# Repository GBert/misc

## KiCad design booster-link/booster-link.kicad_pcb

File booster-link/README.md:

Einfacher Gleisboxbooster
=========================

Siehe auch:
[Stummi Forum Thread](https://stummiforum.de/viewtopic.php?f=7&t=160368&start=50#p1859777)

Optionen:
- ohne öffnen der Gleisbox 
- automatishce Gleisspannungsabschaltung (Stopp) nach 250ms
- direkte Anbindung an die Gleisbox (nur zwei Widerstände + Transistor)

BOM
---
[Reichelt Liste](https://www.reichelt.de/my/1491385)

|Reference	| Value		| Footprint	|
|---------------|---------------|---------------|
|C1,C3,C11	|100nF		|RM2.5		|
|C2		|10uF		|RM2.5		|
|C12		|2,2uF		|MKS 2, RM5	|
|D1		|1N4148		|DO33		|
|D2,D3		|LED 2mA	|5mm		|
|Q1		|BC337		|TO-92		|
|R1,R3,R5,R7	|1k5 Ohm	|0207		|
|R2,R4		|390 Ohm	|0207		|
|R11,R12	|100 kOhm	|0207		|
|U1		|MC7805		|TO-220		|
|U2		|6N137		|DIP-8		|
|U3		|NE555		|DIP-8		|
|P1		|Anreihklemme	|RM5.04		|
|P2		|Pinsocket 2x4	|RM2.54		|
|P3		|Pinheader 2x3	|RM2.54		|
|P4		|Pinheader 1x3	|RM2.54		|
|		|Jumper		|RM2.54		|
|		|Spcket		|DIP-8		|

BOM (über interne Signale der Gleisbox)
---------------------------------------
|Reference	| Value		| Footprint	|
|---------------|---------------|---------------|
|Q21		|BC337		|TO-92		|
|R21		|1k5 Ohm	|0207		|
|R22		|390 Ohm	|0207		|

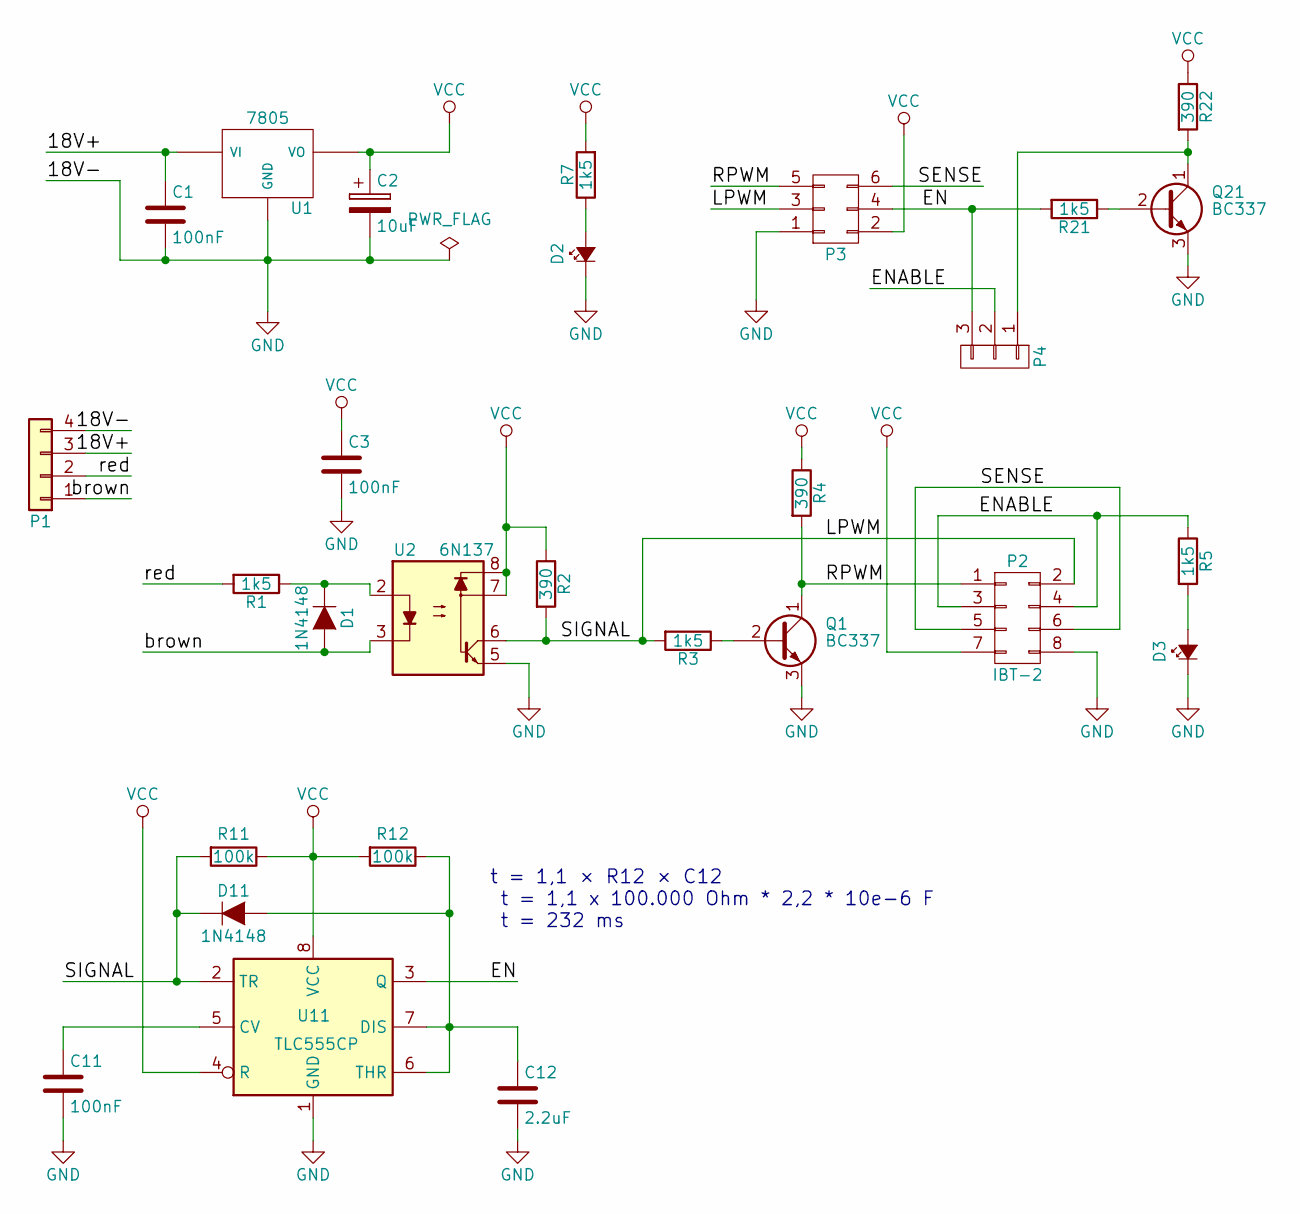
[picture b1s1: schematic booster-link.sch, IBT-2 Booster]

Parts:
C1, C3, C11: 100nF; cnp_3mm_disc
C2: 10uF; CP_4x5mm
C12: 2.2uF; C_Rect_L7_W2_P5
D1, D11: 1N4148; diode_do35
D2, D3: Led_Small; LED-5MM
P1: Conn_01x04; akl0711,5-4
P2: IBT-2; Socket_Strip_Straight_2x04
P3: EXTCON; Pin_Header_Straight_2x03
P4: CONN_01X03; Pin_Header_Straight_1x03
Q1, Q21: BC337; TO-92_Inline_Narrow_Oval
R1, R3, R5, R7, R21: 1k5; RC03
R2, R4, R22: 390; RC03
R11, R12: 100k; RC03
U1: 7805; TO-220-78xx
U2: 6N137; dil_8-300_socket
U11: TLC555CP; dil_8-300_socket

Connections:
/18V+: C1.1, P1.3, U1.VI
/EN: P3.4, P4.3, R21.2, U11.3 (Q)
/ENABLE: P2.3, P2.4, P4.2, R5.1
/LPWM: D11.2 (K), P2.2, P3.3, R2.2, R3.2, R11.2, U2.6, U11.2 (TR)
/RPWM: P2.1, P3.5, Q1.1 (C), R4.2
/SENSE: P2.5, P2.6, P3.6
/brown: D1.1 (A), P1.1, U2.3
/red: P1.2, R1.2
GND: C1.2, C2.2, C3.2, C11.2, C12.2, D2.1 (K), D3.1 (K), P1.4, P2.8, P3.1, Q1.3 (E), Q21.3 (E), U1.GND, U2.5, U11.1 (GND)
unnamed: C11.1, U11.5 (CV)
unnamed: C12.1, D11.1 (A), R12.1, U11.6 (THR), U11.7 (DIS)
unnamed: D1.2 (K), R1.1, U2.2
unnamed: D2.2 (A), R7.1
unnamed: D3.2 (A), R5.2
unnamed: P4.1, Q21.1 (C), R22.2
unnamed: Q1.2 (B), R3.1
unnamed: Q21.2 (B), R21.1
VCC: C2.1, C3.1, P2.7, P3.2, R2.1, R4.1, R7.2, R11.1, R12.2, R22.1, U1.VO, U2.7, U2.8, U11.4 (R), U11.8 (VCC)

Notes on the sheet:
t = 1,1 × R12 × C12 t = 1,1 x 100.000 Ohm * 2,2 * 10e-6 F t = 232 ms

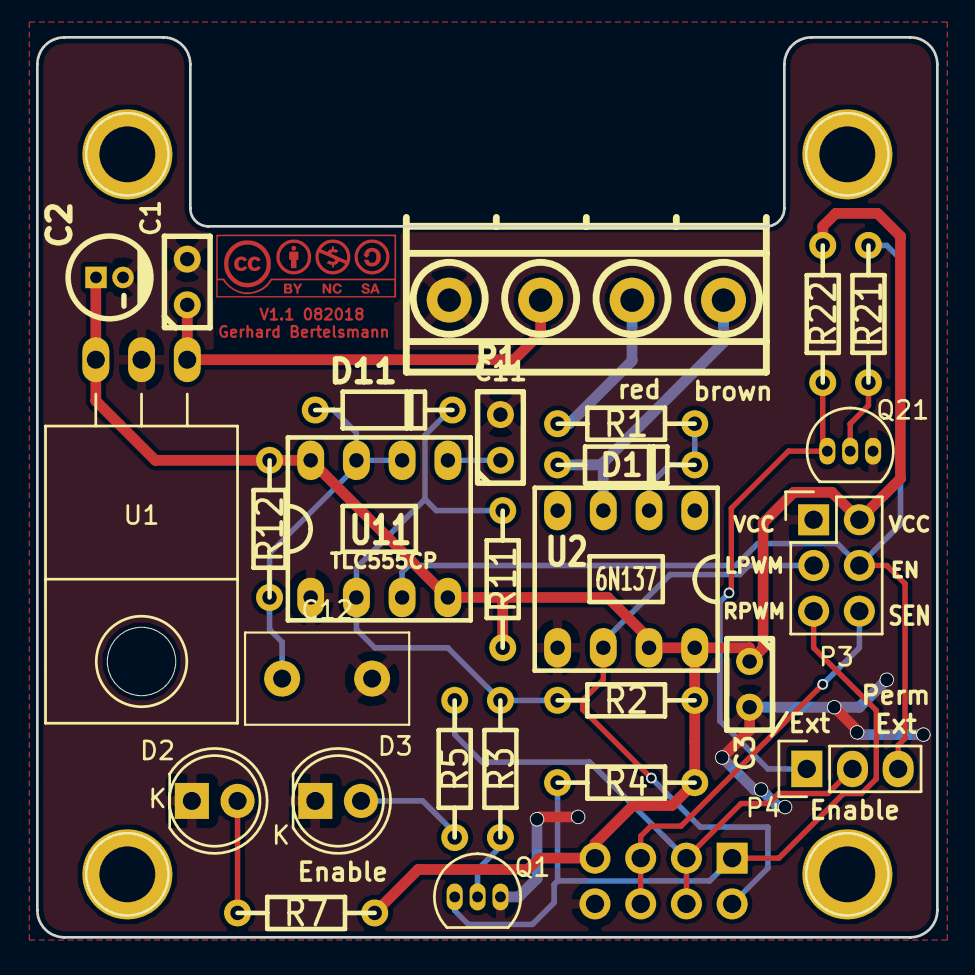
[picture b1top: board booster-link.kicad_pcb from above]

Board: 2 copper layers, 50.0 x 50.0 mm, 28 parts (1 on the bottom side), 18 nets.

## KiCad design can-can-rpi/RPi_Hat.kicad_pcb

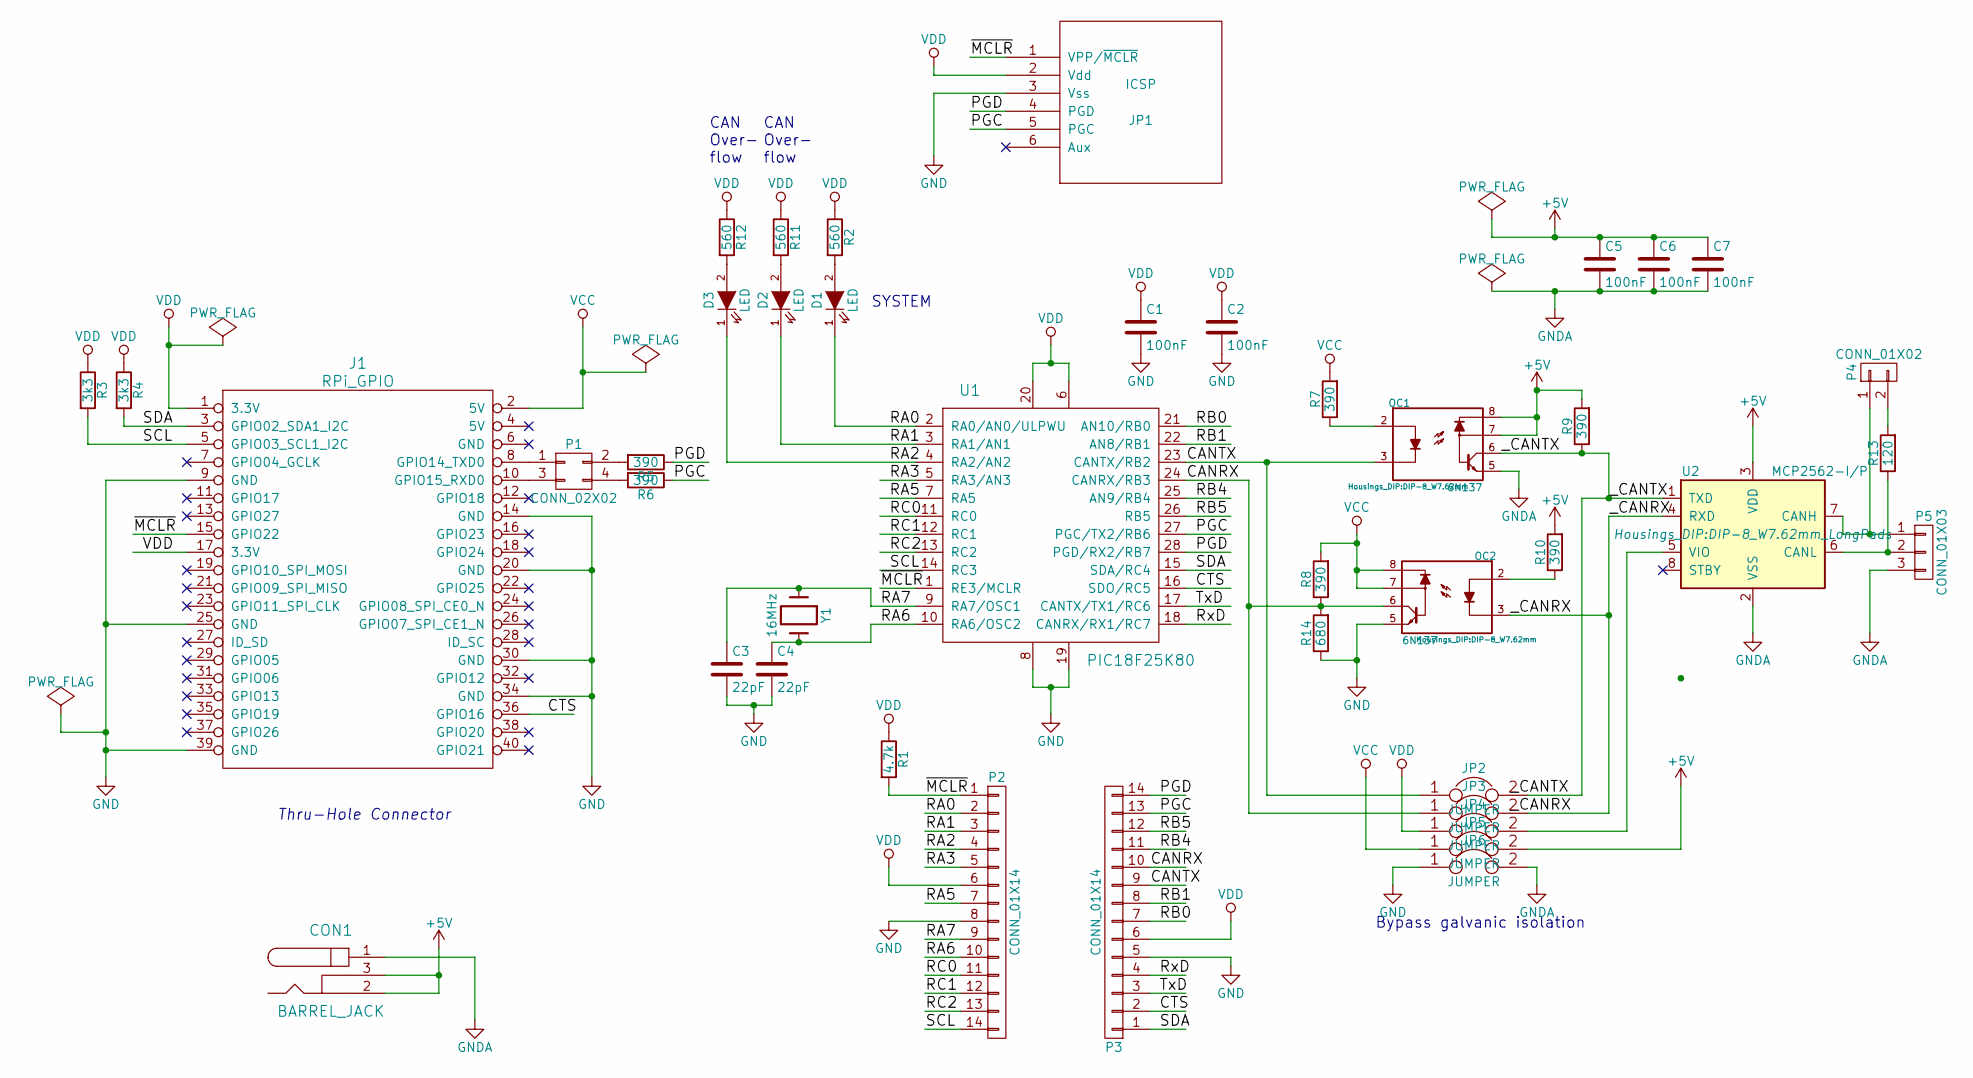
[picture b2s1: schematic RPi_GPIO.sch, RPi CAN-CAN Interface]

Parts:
C1, C2, C5, C6, C7: 100nF; C_Disc_D3_P2.5
C3, C4: 22pF; C_Disc_D3_P2.5
CON1: BARREL_JACK
D1, D2, D3: LED; LED-3MM
J1: RPi_GPIO; Socket_Strip_Straight_2x20
JP1: ICSP
JP2, JP3, JP4, JP5, JP6: JUMPER; SolderWirePad_2x_0-2.54mmDrill
OC1, OC2: 6N137; DIP-8_W7.62mm
P1: CONN_02X02; Pin_Header_Straight_2x02
P2, P3: CONN_01X14; Socket_Strip_Straight_1x14
P4: CONN_01X02; Pin_Header_Straight_1x02
P5: CONN_01X03; Pin_Header_Straight_1x03
R1: 4.7k; Resistor_Horizontal_RM10mm
R2, R11, R12: 560; Resistor_Horizontal_RM10mm
R3, R4: 3k3; Resistor_Horizontal_RM10mm
R5, R6, R7, R8, R9, R10: 390; Resistor_Horizontal_RM10mm
R13: 120; Resistor_Horizontal_RM10mm
R14: 680; Resistor_Horizontal_RM10mm
U1: PIC18F25K80; DIP-28_W7.62mm
U2: MCP2562-I/P; DIP-8_W7.62mm_LongPads
Y1: 16MHz; Crystal_HC49-U_Vertical

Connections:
+5V: C5.1, C6.1, C7.1, CON1.2, CON1.3, JP5.2, OC1.7, OC1.8, R9.2, R10.2, U2.3 (VDD)
/RPi_GPIO/CANRX: JP3.1, OC2.6, P3.10, R8.1, R14.2, U1.24 (CANRX/RB3)
/RPi_GPIO/CANTX: JP2.1, OC1.3, P3.9, U1.23 (CANTX/RB2)
/RPi_GPIO/CTS: J1.36 (GPIO16), P3.2, U1.16 (SDO/RC5)
/RPi_GPIO/PGC: JP1.5 (PGC), P3.13, R6.1, U1.27 (PGC/TX2/RB6)
/RPi_GPIO/PGD: JP1.4 (PGD), P3.14, R5.1, U1.28 (PGD/RX2/RB7)
/RPi_GPIO/RA0: D1.1 (K), P2.2, U1.2 (RA0/AN0/ULPWU)
/RPi_GPIO/RA1: D2.1 (K), P2.3, U1.3 (RA1/AN1)
/RPi_GPIO/RA2: D3.1 (K), P2.4, U1.4 (RA2/AN2)
/RPi_GPIO/RA3: P2.5, U1.5 (RA3/AN3)
/RPi_GPIO/RA5: P2.7, U1.7 (RA5)
/RPi_GPIO/RA6: C4.1, P2.10, U1.10 (RA6/OSC2), Y1.2
/RPi_GPIO/RA7: C3.1, P2.9, U1.9 (RA7/OSC1), Y1.1
/RPi_GPIO/RB0: P3.7, U1.21 (AN10/RB0)
/RPi_GPIO/RB1: P3.8, U1.22 (AN8/RB1)
/RPi_GPIO/RB4: P3.11, U1.25 (AN9/RB4)
/RPi_GPIO/RB5: P3.12, U1.26 (RB5)
/RPi_GPIO/RC0: P2.11, U1.11 (RC0)
/RPi_GPIO/RC1: P2.12, U1.12 (RC1)
/RPi_GPIO/RC2: P2.13, U1.13 (RC2)
/RPi_GPIO/RxD: P3.4, U1.18 (CANRX/RX1/RC7)
/RPi_GPIO/SCL: J1.5 (GPIO03_SCL1_I2C), P2.14, R3.2, U1.14 (RC3)
/RPi_GPIO/SDA: J1.3 (GPIO02_SDA1_I2C), P3.1, R4.2, U1.15 (SDA/RC4)
/RPi_GPIO/TxD: P3.3, U1.17 (CANTX/TX1/RC6)
/RPi_GPIO/_CANRX: JP3.2, OC2.3, U2.4 (RXD)
/RPi_GPIO/_CANTX: JP2.2, OC1.6, R9.1, U2.1 (TXD)
/RPi_GPIO/~MCLR: J1.15 (GPIO22), JP1.1 (VPP/~MCLR), P2.1, R1.2, U1.1 (RE3/MCLR)
GND: C1.2, C2.2, C3.2, C4.2, J1.9 (GND), J1.14 (GND), J1.20 (GND), J1.25 (GND), J1.30 (GND), J1.34 (GND), J1.39 (GND), JP1.3 (Vss), JP6.1, OC2.5, P2.8, P3.5, R14.1, U1.8, U1.19
GNDA: C5.2, C6.2, C7.2, CON1.1, JP6.2, OC1.5, P5.3, U2.2 (VSS)
unnamed: D1.2 (A), R2.2
unnamed: D2.2 (A), R11.2
unnamed: D3.2 (A), R12.2
unnamed: J1.8 (GPIO14_TXD0), P1.1
unnamed: J1.10 (GPIO15_RXD0), P1.3
unnamed: JP4.2, U2.5 (VIO)
unnamed: OC1.2, R7.1
unnamed: OC2.2, R10.1
unnamed: P1.2, R5.2
unnamed: P1.4, R6.2
unnamed: P4.1, P5.1, U2.7 (CANH)
unnamed: P4.2, R13.2
unnamed: P5.2, R13.1, U2.6 (CANL)
VCC: J1.2 (5V), JP5.1, OC2.7, OC2.8, R7.2, R8.2
VDD: C1.1, C2.1, J1.1 (3.3V), J1.17 (3.3V), JP1.2 (Vdd), JP4.1, P2.6, P3.6, R1.1, R2.1, R3.1, R4.1, R11.1, R12.1, U1.6, U1.20

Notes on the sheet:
Thru-Hole Connector
Bypass galvanic isolation
SYSTEM
CAN Over- flow

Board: 2 copper layers, 42 parts (1 on the bottom side), 43 nets, no tracks yet.

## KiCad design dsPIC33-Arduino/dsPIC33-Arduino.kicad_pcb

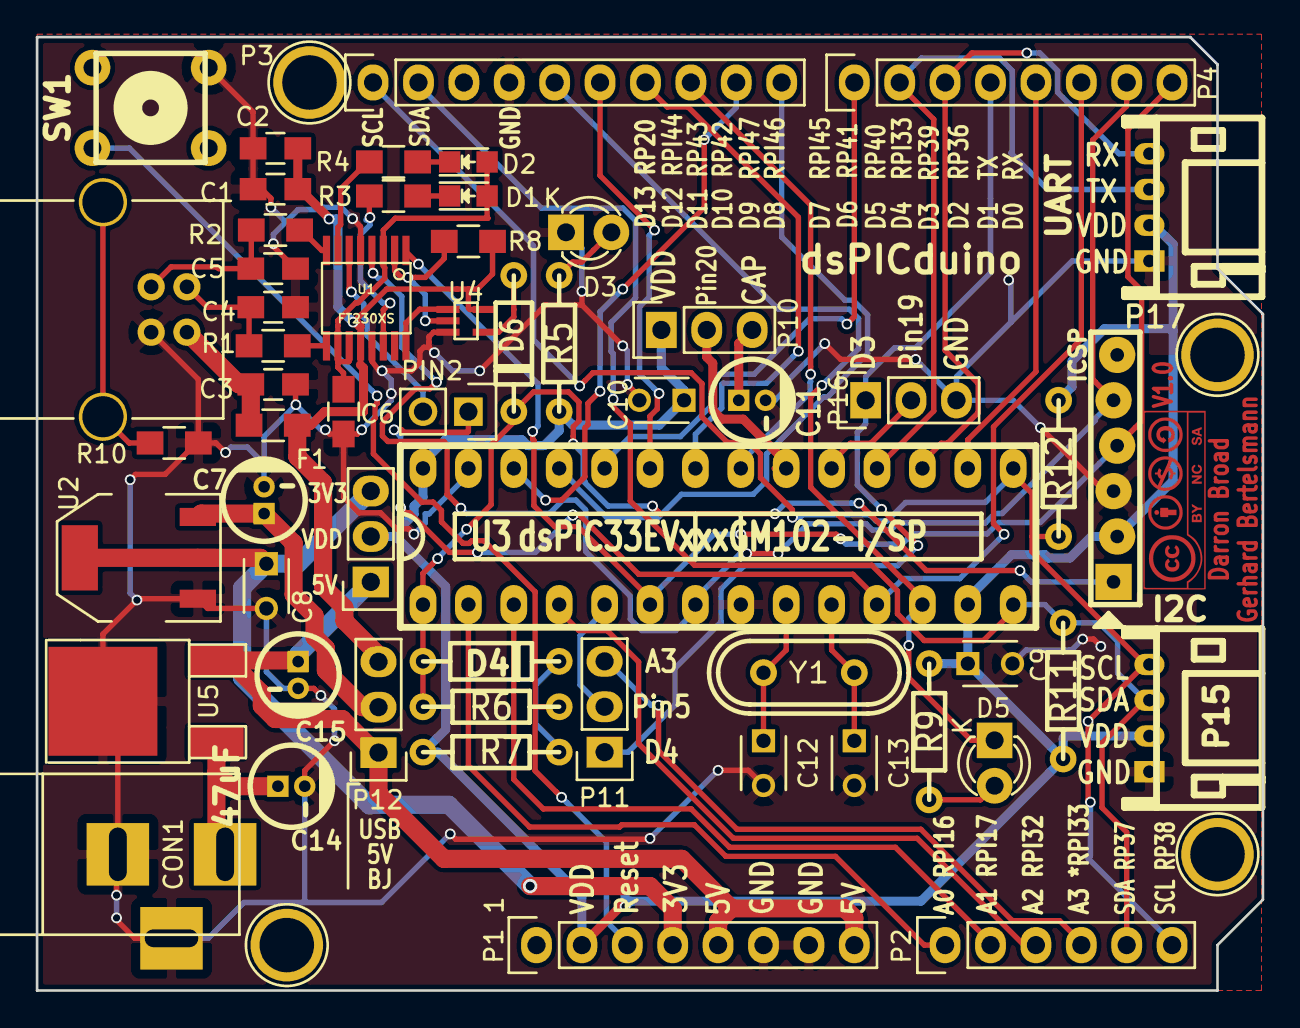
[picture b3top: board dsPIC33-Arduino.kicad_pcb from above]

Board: 2 copper layers, 68.6 x 53.3 mm, 60 parts (0 on the bottom side), 53 nets.

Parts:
C1, C6: 100nF; C_0805_HandSoldering
C2: 4,7uF; C_0805_HandSoldering
C3: 10nF; C_0805_HandSoldering
C4, C5: 47pF; C_0805_HandSoldering
C7, C14, C15: 47uF; CP_4x5mm
C8, C9, C10: 100nF; C_Disc_D3_P2.5
C11: 10uF ESR; CP_4x5mm
C12, C13: 22pF; C_Disc_D3_P2.5
CON1: BARREL_JACK
D1: RX LED; LED_0805
D2: TX LED; LED_0805
D3: Power LED; LED-3MM
D4, D6: BAT43; diode_do35
D5: LED; LED-3MM
F1: Ferrit; R_0805_HandSoldering
JP1: ICSP
P1: Power; Socket_Strip_Arduino_1x08
P2: Analog; Socket_Strip_Arduino_1x06
P3: Digital; Socket_Strip_Arduino_1x10
P4: Digital; Socket_Strip_Arduino_1x08
P5, P6, P7, P8: CONN_1; Arduino_1pin
P9: USB_B
P10: PIN20; Pin_Header_Straight_1x03
P11: PIN5; Pin_Header_Straight_1x03
P12: PWR_IN; Pin_Header_Straight_1x03
P13: PIN2; Pin_Header_Straight_1x02
P14: Power Select; Pin_Header_Straight_1x03
P15: I2C; s4b-ph-kl
P16: PIN19; Pin_Header_Straight_1x03
P17: UART; s4b-ph-kl
R1, R2: 27; R_0805_HandSoldering
R3, R4: 270; R_0805_HandSoldering
R5, R9: 1k5; RC03
R6: 470; RC03
R7: 4k7; RC03
R8: 4k7; R_0805_HandSoldering
R10: 0; R_0805_HandSoldering
R11, R12: 3k3; RC03
SW1: SW_PUSH; PCB_PUSH
U1: FT230XS; ssop-16
U2: LM1117 3V3; SOT-223
U3: dsPIC33EVxxxGM102-I/SP; dil_28-300_socket
U4: 74LVC1G32; SOT-353
U5: 7805; TO-252-2Lead
Y1: Crystal; crystal_hc-49s

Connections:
+3V3: C8.1, P1.4, P14.3, U2.2
+5V: C15.1, P1.5, P1.8, P12.1, P14.1, U5.VO
/2: P4.6, P13.1, U3.11
/3(**): P4.5, U3.16
/4: P4.4, P11.1, P16.1
/5(**): P4.3, P17.4, U3.17
/6(**): P4.2, P17.3, U3.18
/7: P4.1, U3.24
/8: P3.10, U3.25
/9(**): P3.9, U3.26
/10(**/SS): P3.8, U3.21
/11(**/MOSI): P3.7, U3.22
/12(MISO): P3.6, U3.23
/13(SCK): D5.1, P3.5, U3.12
/A0: P2.1, U3.2
/A1: P2.2, U3.3
/A2: P2.3, U3.4
/A3: P2.4, P11.3
/CTS: P13.2, U1.6
/PrgEn: U1.16, U4.1
/RTS: R8.1, U1.2, U4.2
/RX: JP1.4, P4.8, U1.1, U3.6
/SCL: P2.6, P3.1, P15.4, R12.2, U3.15
/SDA: P2.5, P3.2, P15.3, R11.2, U3.14
/TX: JP1.5, P4.7, U1.4, U3.7
/VI: C14.1, CON1.1, U5.VI
/~MCLR~: D4.1, D6.2, JP1.1, R6.1, U3.1
/~RESET~: P1.3, R6.2, SW1.2
GND: C1.2, C2.2, C3.2, C4.2, C5.2, C6.2, C7.2, C8.2, C9.2, C10.2, C11.2, C12.2, C13.2, C14.2, C15.2, CON1.2, CON1.3, D3.1, JP1.3, P1.6, P1.7, P3.4, P9.4, P15.1, P16.3, P17.1, R10.1, SW1.1, U1.5, U1.13, U2.1, U3.8, U3.27, U4.3, U5.GND
unnamed: C3.1, F1.2, P9.1
unnamed: C4.1, P9.2, R1.2
unnamed: C5.1, P9.3, R2.2
unnamed: C6.1, D1.2, D2.2, U1.3, U1.10, U1.11
unnamed: C7.1, P12.2, U2.3
unnamed: C11.1, P10.3
unnamed: C12.1, U3.9, Y1.1
unnamed: C13.1, U3.10, Y1.2
unnamed: D1.1, R3.1
unnamed: D2.1, R4.1
unnamed: D3.2, R5.2
unnamed: D4.2, R7.2
unnamed: D5.2, R9.2
unnamed: D6.1, U4.4
unnamed: P9.5, R10.2
unnamed: P10.2, U3.20
unnamed: P11.2, U3.5
unnamed: P16.2, U3.19
unnamed: R1.1, U1.9
unnamed: R2.1, U1.8
unnamed: R3.2, U1.14
unnamed: R4.2, U1.7
VCC: C1.1, C2.1, F1.1, P12.3, R8.2, U1.12, U4.5
VDD: C9.1, C10.1, JP1.2, P1.2, P10.1, P14.2, P15.2, P17.2, R5.1, R7.1, R9.1, R11.1, R12.1, U3.13, U3.28

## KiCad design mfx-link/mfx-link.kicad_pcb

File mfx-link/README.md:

mfx-Booster/Link
================

Booster incl. mfx-R&uuml;kmeldung zusammen mit einem IBT-2 Modul

Kombination aus [mfx-R&uuml;ckmelder](http://www.persmodelrailroad.net/mfx_boost.html) und [DCC Booster](http://www.trainelectronics.com/DCC_Arduino/DCC_Booster), der auch MM und mfx kann

Der mfx-Booster/Link bietet zusammen mit dem IBT-2 Modul und einem entsprechenden Netzteil eine kosteng&uuml;nstige Erweiterung f&uuml;r eine leistungsstarke Zentrale (10A).

Bauteile
--------
[Reichelt Warenkorb](https://www.reichelt.de/my/1341110)

Geeignete &Uuml;bertrager:
```
Murata 56100C bzw 56T100C (primaer 2 Windungen -> 1:50)
oder handgewickelt auf Ferrit-Ring
```

Errata
------
Version 1.1:

Der Platinen-Aufdruck der Schottky-Diode (BAT43) D12 nahe dem Resetknopf ist falsch. Die Kathode muss in Richtung Mini-Taster zeigen.

Verdrahtung:
------------

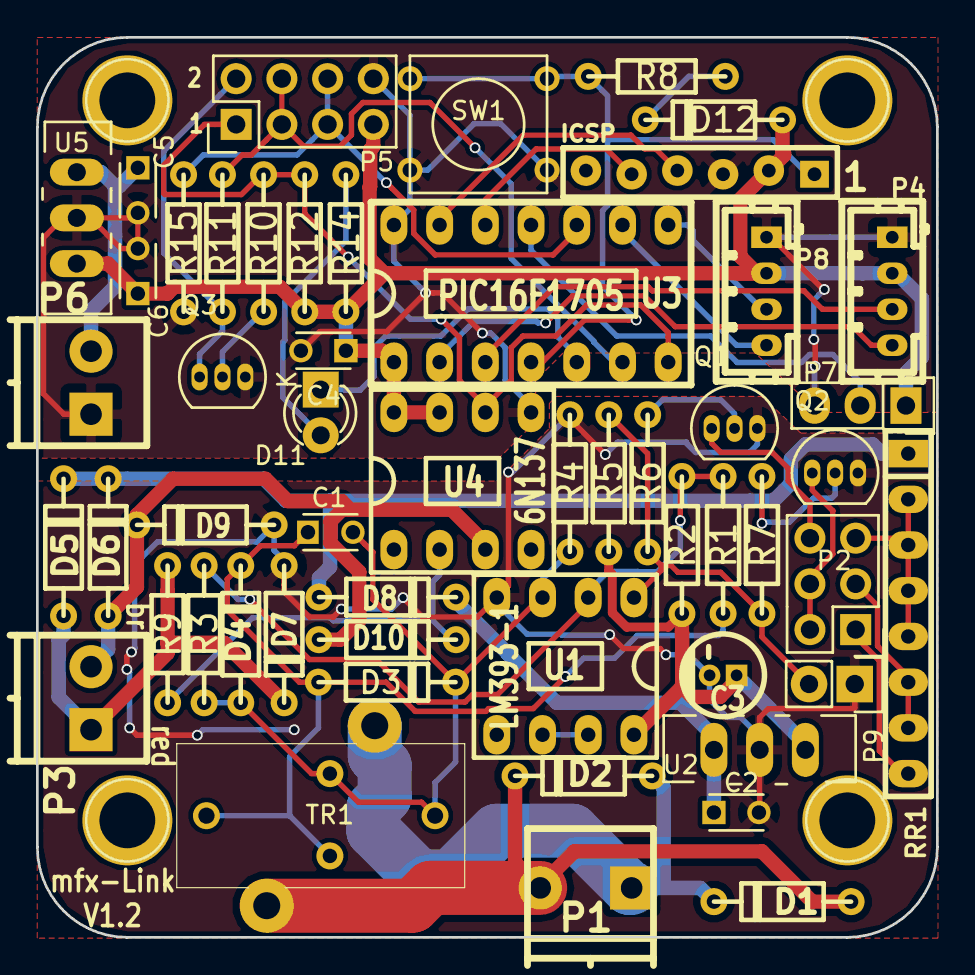
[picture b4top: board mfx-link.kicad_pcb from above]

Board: 2 copper layers, 50.0 x 50.0 mm, 53 parts (0 on the bottom side), 40 nets.

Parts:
C1, C2, C4, C5, C6: 100nF; C_Disc_D3_P2.5
C3: CP; CP_4x7mm
D1, D2, D5, D6, D7, D8, D9: UF4007; diode_do35
D3, D4, D10: 1N4148; diode_do35
D11: LED; LED-3MM
D12: BAT43; diode_do35
JP1: ICSP
P1, P3, P6: CONN_01X02; pt_1,5-2-3,5-h
P2: CONN_02X03; Pin_Header_Straight_2x03
P4: Grove I2C; b4b-ph-kl
P5: IBT-2; Pin_Header_Straight_2x04
P7: CONN_01X03; Pin_Header_Straight_1x03
P8: Grove UART; b4b-ph-kl
P9: MFX; Pin_Header_Straight_1x02
Q1, Q2: BC517; TO-92_Inline_Narrow_Oval
Q3: BC547; TO-92_Inline_Narrow_Oval
R1: 22; RC03
R2, R4, R5, R8: 4k7; RC03
R3: 82; RC03
R6, R7, R10: 1k; RC03
R9, R14: 1k5; RC03
R11: 330; RC03
R12: 390; RC03
R15: 10k; RC03
RR1: RR7; r-sil_8
SW1: SW_PUSH; SW_PUSH_SMALL
TR1: TRANSF1; Murata56000C
U1: LM393-1; dil_8-300_socket
U2, U5: 7805; TO-220_Neutral123_Vertical_LargePads
U3: PIC16F1705; dil_14-300_socket
U4: 6N137; dil_8-300_socket

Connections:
/ENABLE: P5.3, P5.4, R11.1, U3.6
/GVI: C2.1, D8.2, U2.1
/MCLR: JP1.1, R8.1, SW1.1, U3.4
/PGC: JP1.5, U3.12
/PGD: JP1.4, U3.13
/PULSE: P5.1, R10.1, R12.1, U3.7, U4.6
/RxD: P8.4, U3.9
/SCL: P4.4, U3.2
/SDA: P4.3, U3.3
/SENSE: P5.5, P5.6, R15.2, U3.10
/TxD: P8.3, U3.8
/VI: C5.1, P6.2, U5.1
/boost_1: D1.2, D2.1, P1.1, TR1.2
/boost_2: D1.1, D2.2, P1.2, TR1.1
/brown: D6.1, D9.2, D10.1, P3.2, U4.3
/red: D5.1, D7.2, P3.1, R9.2
GND: C2.2, C3.2, D7.1, D9.1, P9.1, Q1.3, Q2.3, R4.1, U1.4, U2.2
GNDA: C4.2, C5.2, C6.2, JP1.3, P4.1, P5.8, P6.1, P7.3, P8.1, Q3.3, R15.1, SW1.2, U3.14, U4.5, U5.2
unnamed: C1.1, D3.1, D4.2, R1.2, TR1.4
unnamed: C1.2, D3.2, D4.1, R3.1, R4.2, TR1.3, U1.3
unnamed: D5.2, D6.2, D8.1, RR1.1
unnamed: D10.2, R9.1, U4.2
unnamed: D11.1, U3.5
unnamed: D11.2, R14.1
unnamed: D12.1, R8.2
unnamed: P2.1, RR1.8
unnamed: P2.2, P2.4, Q2.1
unnamed: P2.3, RR1.6, RR1.7
unnamed: P2.5, RR1.2, RR1.3, RR1.4, RR1.5
unnamed: P2.6, Q1.1
unnamed: P5.2, Q3.1, R11.2
unnamed: P7.2, U3.11
unnamed: P9.2, R5.1, R6.2, R7.2, U1.1
unnamed: Q1.2, R6.1
unnamed: Q2.2, R7.1
unnamed: Q3.2, R10.2
unnamed: R1.1, R2.1, R3.2, U1.2
unnamed: U1.6, U1.7
VCC: C3.1, R2.2, R5.2, U1.8, U2.3
VDD: C4.1, C6.1, D12.2, JP1.2, P4.2, P5.7, P7.1, P8.2, R12.2, R14.2, U3.1, U4.7, U4.8, U5.3

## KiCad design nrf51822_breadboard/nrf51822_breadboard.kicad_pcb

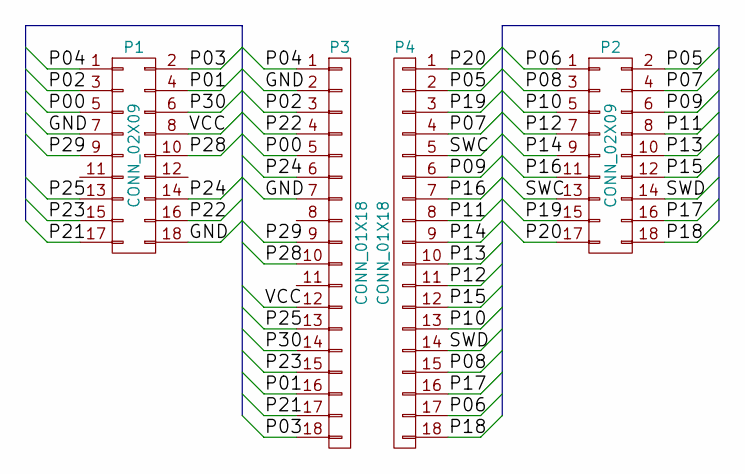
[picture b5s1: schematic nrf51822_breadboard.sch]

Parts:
P1, P2: CONN_02X09; PinHeader_2x09_P2.00mm_Vertical
P3, P4: CONN_01X18; Pin_Header_Straight_1x18

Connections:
/GND: P1.7, P1.18, P3.2, P3.7
/P00: P1.5, P3.5
/P01: P1.4, P3.16
/P02: P1.3, P3.3
/P03: P1.2, P3.18
/P04: P1.1, P3.1
/P05: P2.2, P4.2
/P06: P2.1, P4.17
/P07: P2.4, P4.4
/P08: P2.3, P4.15
/P09: P2.6, P4.6
/P10: P2.5, P4.13
/P11: P2.8, P4.8
/P12: P2.7, P4.11
/P13: P2.10, P4.10
/P14: P2.9, P4.9
/P15: P2.12, P4.12
/P16: P2.11, P4.7
/P17: P2.16, P4.16
/P18: P2.18, P4.18
/P19: P2.15, P4.3
/P20: P2.17, P4.1
/P21: P1.17, P3.17
/P22: P1.16, P3.4
/P23: P1.15, P3.15
/P24: P1.14, P3.6
/P25: P1.13, P3.13
/P28: P1.10, P3.10
/P29: P1.9, P3.9
/P30: P1.6, P3.14
/SWC: P2.13, P4.5
/SWD: P2.14, P4.14
/VCC: P1.8, P3.12

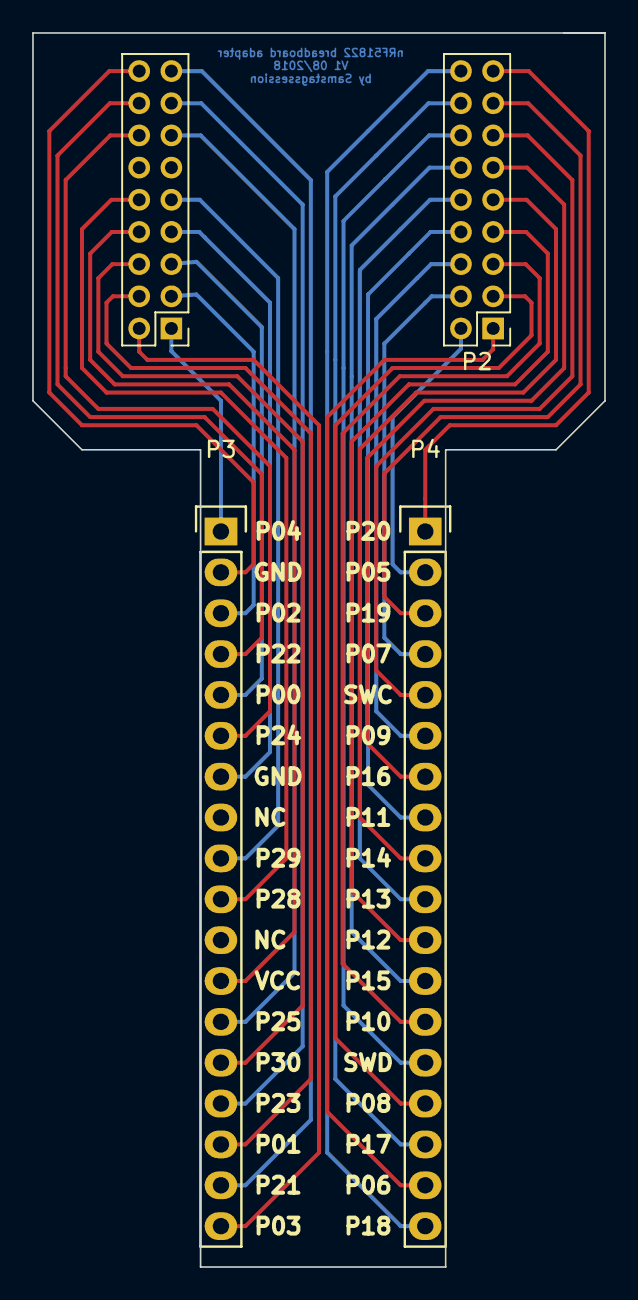
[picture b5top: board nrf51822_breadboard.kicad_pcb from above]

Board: 2 copper layers, 35.6 x 76.7 mm, 4 parts (0 on the bottom side), 33 nets.

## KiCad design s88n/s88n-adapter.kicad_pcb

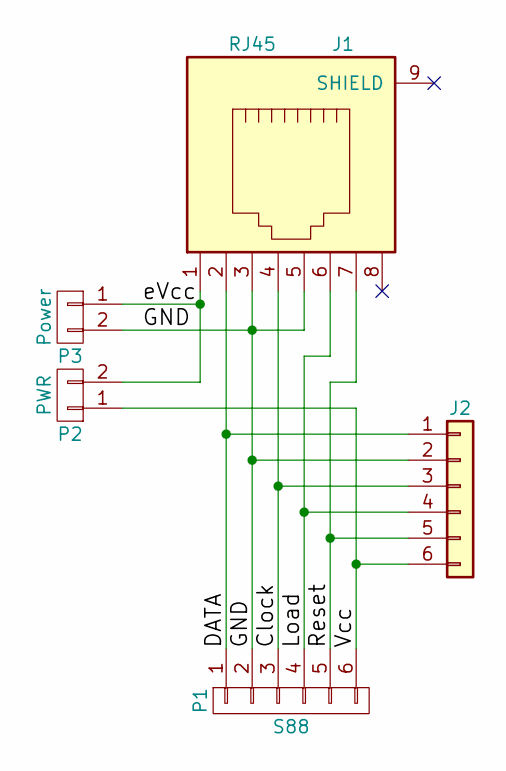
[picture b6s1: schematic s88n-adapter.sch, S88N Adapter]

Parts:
J1: RJ45; megb8-8
J2: Conn_01x06; Pin_Header_Straight_1x06_Pitch2.54mm
P1: S88; Pin_Header_Angled_1x06
P2: PWR; Pin_Header_Straight_1x02
P3: Power; pt_1,5-2-3,5-h

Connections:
/Clock: J1.4, J2.3, P1.3
/DATA: J1.2, J2.1, P1.1
/GND: J1.3, J1.5, J2.2, P1.2, P3.2
/Load: J1.6, J2.4, P1.4
/Reset: J1.7, J2.5, P1.5
/Vcc: J2.6, P1.6, P2.1
/eVcc: J1.1, P2.2, P3.1

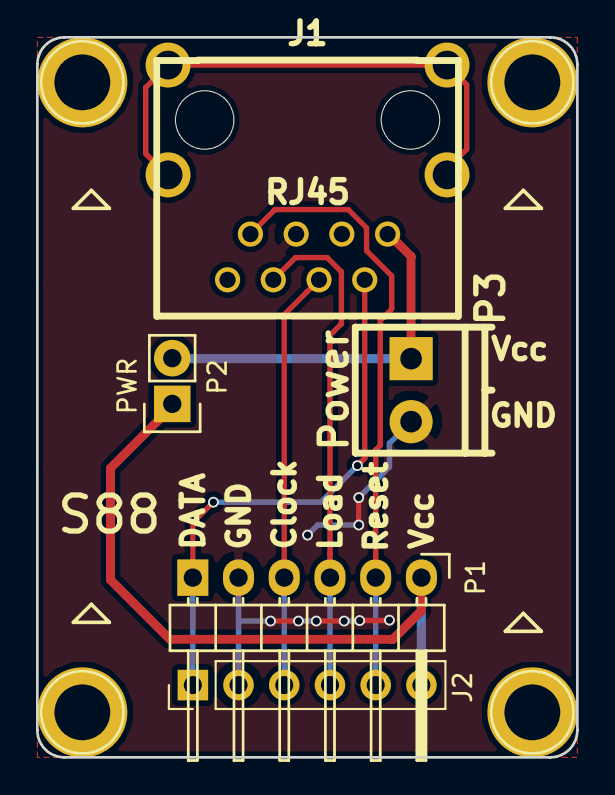
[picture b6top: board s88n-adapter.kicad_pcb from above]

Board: 2 copper layers, 30.0 x 40.0 mm, 5 parts (0 on the bottom side), 7 nets.

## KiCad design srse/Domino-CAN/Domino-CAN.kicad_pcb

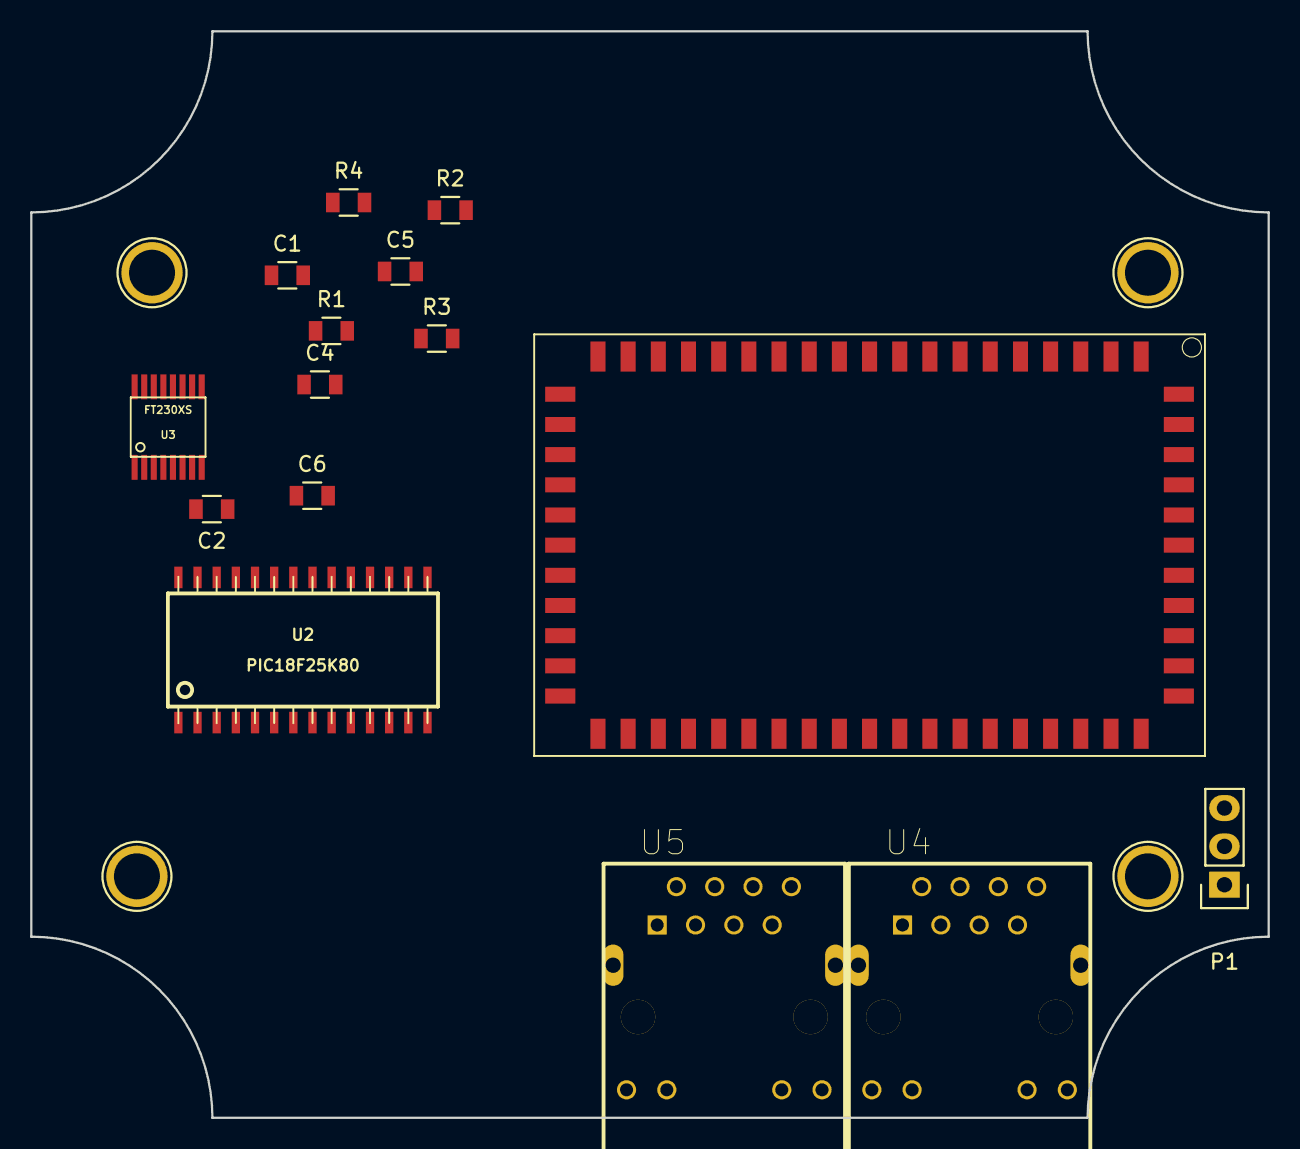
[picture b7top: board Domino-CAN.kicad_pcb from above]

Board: 2 copper layers, 82.0 x 72.0 mm, 19 parts (0 on the bottom side), 13 nets, no tracks yet.

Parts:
C1, C2: 47pF; R_0805_HandSoldering_II
C4, C5: 100nF; R_0805_HandSoldering_II
C6: 4.7uF; R_0805_HandSoldering_II
P1: UART; Pin_Header_Straight_1x03
R1, R2: 27; R_0805_HandSoldering_II
R3, R4: 220; R_0805_HandSoldering_II
RF1, RF2, RF3, RF4: 1pin
U1: DOMINO_CORE; DOMINO
U2: PIC18F25K80; soic-28
U3: FT230XS; ssop-16
U4, U5: HR911105A; RJ45ALED_1PRIMARY

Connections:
/RxD: U2.27, U3.4
/TxD: U2.28, U3.1
/USBDM: C2.1, R1.2, U1.52
/USBDP: C1.1, R2.2, U1.53
GND: C1.2, C2.2, C4.2, C5.2, C6.2, P1.1, U1.1, U1.2, U1.3, U1.10, U1.35, U1.45, U1.51, U1.57, U1.58, U1.60, U2.8, U2.19, U3.5, U3.13
unnamed: U3.3, U3.10, U3.11
unnamed: P1.2, U1.21
unnamed: P1.3, U1.20
unnamed: R1.1, U3.9
unnamed: R2.1, U3.8
unnamed: R3.2, U3.14
unnamed: R4.2, U3.7
VCC: C4.1, C5.1, C6.1, U3.12
